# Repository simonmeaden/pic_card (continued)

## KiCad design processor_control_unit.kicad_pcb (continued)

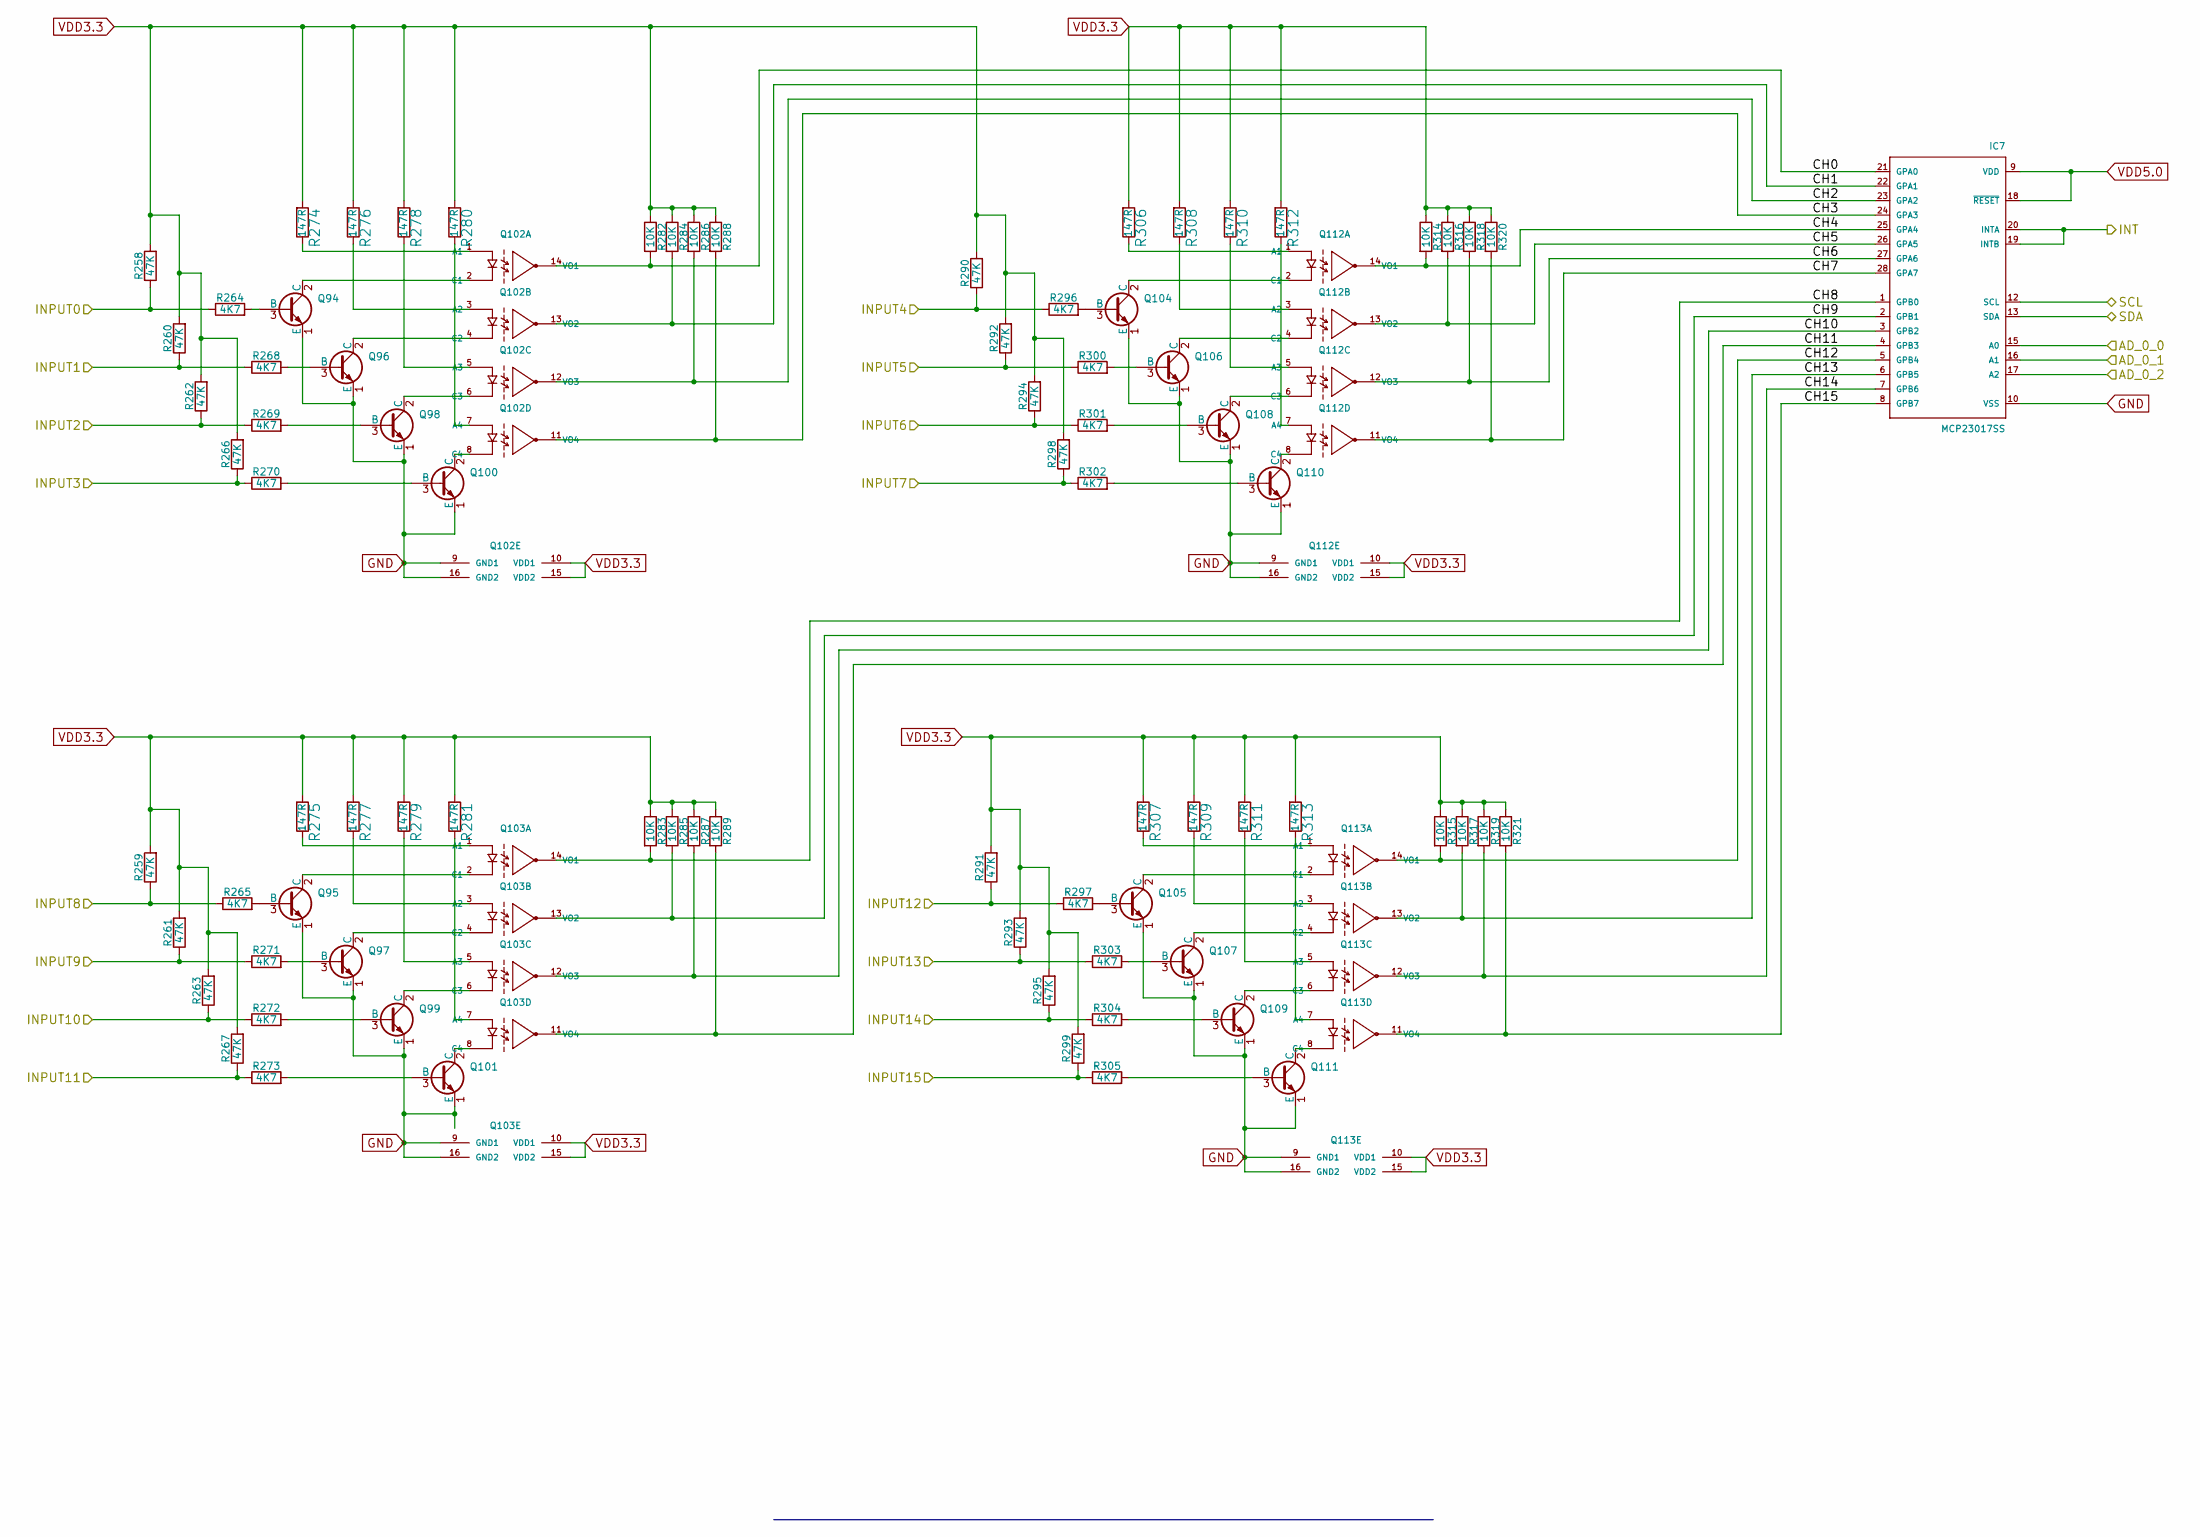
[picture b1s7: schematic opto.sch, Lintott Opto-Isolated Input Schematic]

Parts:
IC7: MCP23017SS; SSOP28
Q94, Q95, Q96, Q97, Q98, Q99, Q100, Q101, Q104, Q105, Q106, Q107, Q108, Q109, Q110, Q111: 2DD2656; SOT-323-DIODES_INC
Q102, Q103, Q112, Q113: ACSL-6400; SO-16-N
R258, R259, R260, R261, R262, R263, R266, R267, R290, R291, R292, R293, R294, R295, R298, R299: 47K; R_0805_2012Metric
R264, R265, R268, R269, R270, R271, R272, R273, R296, R297, R300, R301, R302, R303, R304, R305: 4K7; R_0805_2012Metric
R274, R275, R276, R277, R278, R279, R280, R281, R306, R307, R308, R309, R310, R311, R312, R313: 147R; R_0805_2012Metric
R282, R283, R284, R285, R286, R287, R288, R289, R314, R315, R316, R317, R318, R319, R320, R321: 10K; R_0805_2012Metric

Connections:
/IN-0: R258.1, R264.1; also elsewhere on the board
/IN-1: R260.1, R268.1; also elsewhere on the board
/IN-2: R262.1, R269.1; also elsewhere on the board
/IN-3: R266.1, R270.1; also elsewhere on the board
/IN-4: R290.1, R296.1; also elsewhere on the board
/IN-5: R292.1, R300.1; also elsewhere on the board
/IN-6: R294.1, R301.1; also elsewhere on the board
/IN-7: R298.1, R302.1; also elsewhere on the board
/IN-8: R259.1, R265.1; also elsewhere on the board
/IN-9: R261.1, R271.1; also elsewhere on the board
/IN-10: R263.1, R272.1; also elsewhere on the board
/IN-11: R267.1, R273.1; also elsewhere on the board
/IN-12: R291.1, R297.1; also elsewhere on the board
/IN-13: R293.1, R303.1; also elsewhere on the board
/IN-14: R295.1, R304.1; also elsewhere on the board
/IN-15: R299.1, R305.1; also elsewhere on the board
/Open Collector Buffered Outputs/SCL: IC7.12 (SCL); also elsewhere on the board
/Open Collector Buffered Outputs/SDA: IC7.13 (SDA); also elsewhere on the board
/Opto Isolated Inputs 1/CH0: IC7.21 (GPA0), Q102.14 (VO1), R282.2
/Opto Isolated Inputs 1/CH1: IC7.22 (GPA1), Q102.13 (VO2), R284.2
/Opto Isolated Inputs 1/CH2: IC7.23 (GPA2), Q102.12 (VO3), R286.2
/Opto Isolated Inputs 1/CH3: IC7.24 (GPA3), Q102.11 (VO4), R288.2
/Opto Isolated Inputs 1/CH4: IC7.25 (GPA4), Q112.14 (VO1), R314.2
/Opto Isolated Inputs 1/CH5: IC7.26 (GPA5), Q112.13 (VO2), R316.2
/Opto Isolated Inputs 1/CH6: IC7.27 (GPA6), Q112.12 (VO3), R318.2
/Opto Isolated Inputs 1/CH7: IC7.28 (GPA7), Q112.11 (VO4), R320.2
/Opto Isolated Inputs 1/CH8: IC7.1 (GPB0), Q103.14 (VO1), R283.2
/Opto Isolated Inputs 1/CH9: IC7.2 (GPB1), Q103.13 (VO2), R285.2
/Opto Isolated Inputs 1/CH10: IC7.3 (GPB2), Q103.12 (VO3), R287.2
/Opto Isolated Inputs 1/CH11: IC7.4 (GPB3), Q103.11 (VO4), R289.2
/Opto Isolated Inputs 1/CH12: IC7.5 (GPB4), Q113.14 (VO1), R315.2
/Opto Isolated Inputs 1/CH13: IC7.6 (GPB5), Q113.13 (VO2), R317.2
/Opto Isolated Inputs 1/CH14: IC7.7 (GPB6), Q113.12 (VO3), R319.2
/Opto Isolated Inputs 1/CH15: IC7.8 (GPB7), Q113.11 (VO4), R321.2
/Opto Isolated Inputs 1/INT: IC7.19 (INTB), IC7.20 (INTA); also elsewhere on the board
GND: IC7.10 (VSS), IC7.15 (A0), IC7.16 (A1), IC7.17 (A2), Q94.1 (E), Q95.1 (E), Q96.1 (E), Q97.1 (E), Q98.1 (E), Q99.1 (E), Q100.1 (E), Q101.1 (E), Q102.9 (GND1), Q102.16 (GND2), Q103.9 (GND1), Q103.16 (GND2), Q104.1 (E), Q105.1 (E), Q106.1 (E), Q107.1 (E), Q108.1 (E), Q109.1 (E), Q110.1 (E), Q111.1 (E), Q112.9 (GND1), Q112.16 (GND2), Q113.9 (GND1), Q113.16 (GND2); also elsewhere on the board
unnamed: Q94.3 (B), R264.2
unnamed: Q95.3 (B), R265.2
unnamed: Q96.3 (B), R268.2
unnamed: Q97.3 (B), R271.2
unnamed: Q98.3 (B), R269.2
unnamed: Q99.3 (B), R272.2
unnamed: Q100.2 (C), Q102.8 (C4)
unnamed: Q100.3 (B), R270.2
unnamed: Q101.2 (C), Q103.8 (C4)
unnamed: Q101.3 (B), R273.2
unnamed: Q102.1 (A1), R274.1
unnamed: Q94.2 (C), Q102.2 (C1)
unnamed: Q102.3 (A2), R276.1
unnamed: Q96.2 (C), Q102.4 (C2)
unnamed: Q102.5 (A3), R278.1
unnamed: Q98.2 (C), Q102.6 (C3)
unnamed: Q102.7 (A4), R280.1
unnamed: Q103.1 (A1), R275.1
unnamed: Q95.2 (C), Q103.2 (C1)
unnamed: Q103.3 (A2), R277.1
unnamed: Q97.2 (C), Q103.4 (C2)
unnamed: Q103.5 (A3), R279.1
unnamed: Q99.2 (C), Q103.6 (C3)
unnamed: Q103.7 (A4), R281.1
unnamed: Q104.2 (C), Q112.2 (C1)
unnamed: Q104.3 (B), R296.2
unnamed: Q105.2 (C), Q113.2 (C1)
unnamed: Q105.3 (B), R297.2
unnamed: Q106.2 (C), Q112.4 (C2)
unnamed: Q106.3 (B), R300.2
unnamed: Q107.2 (C), Q113.4 (C2)
unnamed: Q107.3 (B), R303.2
unnamed: Q108.2 (C), Q112.6 (C3)
unnamed: Q108.3 (B), R301.2
unnamed: Q109.2 (C), Q113.6 (C3)
unnamed: Q109.3 (B), R304.2
unnamed: Q110.2 (C), Q112.8 (C4)
unnamed: Q110.3 (B), R302.2
unnamed: Q111.2 (C), Q113.8 (C4)
unnamed: Q111.3 (B), R305.2
unnamed: Q112.1 (A1), R306.1
unnamed: Q112.3 (A2), R308.1
unnamed: Q112.5 (A3), R310.1
unnamed: Q112.7 (A4), R312.1
unnamed: Q113.1 (A1), R307.1
unnamed: Q113.3 (A2), R309.1
unnamed: Q113.5 (A3), R311.1
unnamed: Q113.7 (A4), R313.1
VDD3.3: Q102.10 (VDD1), Q102.15 (VDD2), Q103.10 (VDD1), Q103.15 (VDD2), Q112.10 (VDD1), Q112.15 (VDD2), Q113.10 (VDD1), Q113.15 (VDD2), R258.2, R259.2, R260.2, R261.2, R262.2, R263.2, R266.2, R267.2, R274.2, R275.2, R276.2, R277.2, R278.2, R279.2, R280.2, R281.2, R282.1, R283.1, R284.1, R285.1, R286.1, R287.1, R288.1, R289.1, R290.2, R291.2, R292.2, R293.2, R294.2, R295.2, R298.2, R299.2, R306.2, R307.2, R308.2, R309.2, R310.2, R311.2, R312.2, R313.2, R314.1, R315.1, R316.1, R317.1, R318.1, R319.1, R320.1, R321.1; also elsewhere on the board
VDD5.0: IC7.9 (VDD), IC7.18 (~RESET); also elsewhere on the board

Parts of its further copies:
IC4, IC5, IC6: MCP23017SS; SSOP28
Q34, Q35, Q36, Q37, Q38, Q39, Q40, Q41, Q44, Q45, Q46, Q47, Q48, Q49, Q50, Q51, Q54, Q55, Q56, Q57, Q58, Q59, Q60, Q61, Q64, Q65, Q66, Q67, Q68, Q69, Q70, Q71, Q74, Q75, Q76, Q77, Q78, Q79, Q80, Q81, Q84, Q85, Q86, Q87, Q88, Q89, Q90, Q91: 2DD2656; SOT-323-DIODES_INC
Q42, Q43, Q52, Q53, Q62, Q63, Q72, Q73, Q82, Q83, Q92, Q93: ACSL-6400; SO-16-N
R66, R67, R68, R69, R70, R71, R74, R75, R98, R99, R100, R101, R102, R103, R106, R107, R130, R131, R132, R133, R134, R135, R138, R139, R162, R163, R164, R165, R166, R167, R170, R171, R194, R195, R196, R197, R198, R199, R202, R203, R226, R227, R228, R229, R230, R231, R234, R235: 47K; R_0805_2012Metric
R72, R73, R76, R77, R78, R79, R80, R81, R104, R105, R108, R109, R110, R111, R112, R113, R136, R137, R140, R141, R142, R143, R144, R145, R168, R169, R172, R173, R174, R175, R176, R177, R200, R201, R204, R205, R206, R207, R208, R209, R232, R233, R236, R237, R238, R239, R240, R241: 4K7; R_0805_2012Metric
R82, R83, R84, R85, R86, R87, R88, R89, R114, R115, R116, R117, R118, R119, R120, R121, R146, R147, R148, R149, R150, R151, R152, R153, R178, R179, R180, R181, R182, R183, R184, R185, R210, R211, R212, R213, R214, R215, R216, R217, R242, R243, R244, R245, R246, R247, R248, R249: 147R; R_0805_2012Metric
R90, R91, R92, R93, R94, R95, R96, R97, R122, R123, R124, R125, R126, R127, R128, R129, R154, R155, R156, R157, R158, R159, R160, R161, R186, R187, R188, R189, R190, R191, R192, R193, R218, R219, R220, R221, R222, R223, R224, R225, R250, R251, R252, R253, R254, R255, R256, R257: 10K; R_0805_2012Metric

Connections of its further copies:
+5V: IC4.15 (A0), IC5.16 (A1), IC6.15 (A0), IC6.16 (A1); also elsewhere on the board
/IN-16: R66.1, R72.1; also elsewhere on the board
/IN-17: R68.1, R76.1; also elsewhere on the board
/IN-18: R70.1, R77.1; also elsewhere on the board
/IN-19: R74.1, R78.1; also elsewhere on the board
/IN-20: R98.1, R104.1; also elsewhere on the board
/IN-21: R100.1, R108.1; also elsewhere on the board
/IN-22: R102.1, R109.1; also elsewhere on the board
/IN-23: R106.1, R110.1; also elsewhere on the board
/IN-24: R67.1, R73.1; also elsewhere on the board
/IN-25: R69.1, R79.1; also elsewhere on the board
/IN-26: R71.1, R80.1; also elsewhere on the board
/IN-27: R75.1, R81.1; also elsewhere on the board
/IN-28: R99.1, R105.1; also elsewhere on the board
/IN-29: R101.1, R111.1; also elsewhere on the board
/IN-30: R103.1, R112.1; also elsewhere on the board
/IN-31: R107.1, R113.1; also elsewhere on the board
/IN-32: R130.1, R136.1; also elsewhere on the board
/IN-33: R132.1, R140.1; also elsewhere on the board
/IN-34: R134.1, R141.1; also elsewhere on the board
/IN-35: R138.1, R142.1; also elsewhere on the board
/IN-36: R162.1, R168.1; also elsewhere on the board
/IN-37: R164.1, R172.1; also elsewhere on the board
/IN-38: R166.1, R173.1; also elsewhere on the board
/IN-39: R170.1, R174.1; also elsewhere on the board
/IN-40: R131.1, R137.1; also elsewhere on the board
/IN-41: R133.1, R143.1; also elsewhere on the board
/IN-42: R135.1, R144.1; also elsewhere on the board
/IN-43: R139.1, R145.1; also elsewhere on the board
/IN-44: R163.1, R169.1; also elsewhere on the board
/IN-45: R165.1, R175.1; also elsewhere on the board
/IN-46: R167.1, R176.1; also elsewhere on the board
/IN-47: R171.1, R177.1; also elsewhere on the board
/IN-48: R194.1, R200.1; also elsewhere on the board
/IN-49: R196.1, R204.1; also elsewhere on the board
/IN-50: R198.1, R205.1; also elsewhere on the board
/IN-51: R202.1, R206.1; also elsewhere on the board
/IN-52: R226.1, R232.1; also elsewhere on the board
/IN-53: R228.1, R236.1; also elsewhere on the board
/IN-54: R230.1, R237.1; also elsewhere on the board
/IN-55: R234.1, R238.1; also elsewhere on the board
/IN-56: R195.1, R201.1; also elsewhere on the board
/IN-57: R197.1, R207.1; also elsewhere on the board
/IN-58: R199.1, R208.1; also elsewhere on the board
/IN-59: R203.1, R209.1; also elsewhere on the board
/IN-60: R227.1, R233.1; also elsewhere on the board
/IN-61: R229.1, R239.1; also elsewhere on the board
/IN-62: R231.1, R240.1; also elsewhere on the board
/IN-63: R235.1, R241.1; also elsewhere on the board
/Open Collector Buffered Outputs/SCL: IC4.12 (SCL), IC5.12 (SCL), IC6.12 (SCL); also elsewhere on the board
/Open Collector Buffered Outputs/SDA: IC4.13 (SDA), IC5.13 (SDA), IC6.13 (SDA); also elsewhere on the board
/Opto Isolated Inputs 2/CH0: IC4.21 (GPA0), Q42.14 (VO1), R90.2
/Opto Isolated Inputs 2/CH1: IC4.22 (GPA1), Q42.13 (VO2), R92.2
/Opto Isolated Inputs 2/CH2: IC4.23 (GPA2), Q42.12 (VO3), R94.2
/Opto Isolated Inputs 2/CH3: IC4.24 (GPA3), Q42.11 (VO4), R96.2
/Opto Isolated Inputs 2/CH4: IC4.25 (GPA4), Q52.14 (VO1), R122.2
/Opto Isolated Inputs 2/CH5: IC4.26 (GPA5), Q52.13 (VO2), R124.2
/Opto Isolated Inputs 2/CH6: IC4.27 (GPA6), Q52.12 (VO3), R126.2
/Opto Isolated Inputs 2/CH7: IC4.28 (GPA7), Q52.11 (VO4), R128.2
/Opto Isolated Inputs 2/CH8: IC4.1 (GPB0), Q43.14 (VO1), R91.2
/Opto Isolated Inputs 2/CH9: IC4.2 (GPB1), Q43.13 (VO2), R93.2
/Opto Isolated Inputs 2/CH10: IC4.3 (GPB2), Q43.12 (VO3), R95.2
/Opto Isolated Inputs 2/CH11: IC4.4 (GPB3), Q43.11 (VO4), R97.2
/Opto Isolated Inputs 2/CH12: IC4.5 (GPB4), Q53.14 (VO1), R123.2
/Opto Isolated Inputs 2/CH13: IC4.6 (GPB5), Q53.13 (VO2), R125.2
/Opto Isolated Inputs 2/CH14: IC4.7 (GPB6), Q53.12 (VO3), R127.2
/Opto Isolated Inputs 2/CH15: IC4.8 (GPB7), Q53.11 (VO4), R129.2
/Opto Isolated Inputs 2/INT: IC4.19 (INTB), IC4.20 (INTA); also elsewhere on the board
/Opto Isolated Inputs 3/CH0: IC5.21 (GPA0), Q62.14 (VO1), R154.2
/Opto Isolated Inputs 3/CH1: IC5.22 (GPA1), Q62.13 (VO2), R156.2
/Opto Isolated Inputs 3/CH2: IC5.23 (GPA2), Q62.12 (VO3), R158.2
/Opto Isolated Inputs 3/CH3: IC5.24 (GPA3), Q62.11 (VO4), R160.2
/Opto Isolated Inputs 3/CH4: IC5.25 (GPA4), Q72.14 (VO1), R186.2
/Opto Isolated Inputs 3/CH5: IC5.26 (GPA5), Q72.13 (VO2), R188.2
/Opto Isolated Inputs 3/CH6: IC5.27 (GPA6), Q72.12 (VO3), R190.2
/Opto Isolated Inputs 3/CH7: IC5.28 (GPA7), Q72.11 (VO4), R192.2
/Opto Isolated Inputs 3/CH8: IC5.1 (GPB0), Q63.14 (VO1), R155.2
/Opto Isolated Inputs 3/CH9: IC5.2 (GPB1), Q63.13 (VO2), R157.2
/Opto Isolated Inputs 3/CH10: IC5.3 (GPB2), Q63.12 (VO3), R159.2
/Opto Isolated Inputs 3/CH11: IC5.4 (GPB3), Q63.11 (VO4), R161.2
/Opto Isolated Inputs 3/CH12: IC5.5 (GPB4), Q73.14 (VO1), R187.2
/Opto Isolated Inputs 3/CH13: IC5.6 (GPB5), Q73.13 (VO2), R189.2
/Opto Isolated Inputs 3/CH14: IC5.7 (GPB6), Q73.12 (VO3), R191.2
/Opto Isolated Inputs 3/CH15: IC5.8 (GPB7), Q73.11 (VO4), R193.2
/Opto Isolated Inputs 3/INT: IC5.19 (INTB), IC5.20 (INTA); also elsewhere on the board
/Opto Isolated Inputs 4/CH0: IC6.21 (GPA0), Q82.14 (VO1), R218.2
/Opto Isolated Inputs 4/CH1: IC6.22 (GPA1), Q82.13 (VO2), R220.2
/Opto Isolated Inputs 4/CH2: IC6.23 (GPA2), Q82.12 (VO3), R222.2
/Opto Isolated Inputs 4/CH3: IC6.24 (GPA3), Q82.11 (VO4), R224.2
/Opto Isolated Inputs 4/CH4: IC6.25 (GPA4), Q92.14 (VO1), R250.2
/Opto Isolated Inputs 4/CH5: IC6.26 (GPA5), Q92.13 (VO2), R252.2
/Opto Isolated Inputs 4/CH6: IC6.27 (GPA6), Q92.12 (VO3), R254.2
/Opto Isolated Inputs 4/CH7: IC6.28 (GPA7), Q92.11 (VO4), R256.2
/Opto Isolated Inputs 4/CH8: IC6.1 (GPB0), Q83.14 (VO1), R219.2
/Opto Isolated Inputs 4/CH9: IC6.2 (GPB1), Q83.13 (VO2), R221.2
/Opto Isolated Inputs 4/CH10: IC6.3 (GPB2), Q83.12 (VO3), R223.2
/Opto Isolated Inputs 4/CH11: IC6.4 (GPB3), Q83.11 (VO4), R225.2
/Opto Isolated Inputs 4/CH12: IC6.5 (GPB4), Q93.14 (VO1), R251.2
/Opto Isolated Inputs 4/CH13: IC6.6 (GPB5), Q93.13 (VO2), R253.2
/Opto Isolated Inputs 4/CH14: IC6.7 (GPB6), Q93.12 (VO3), R255.2
/Opto Isolated Inputs 4/CH15: IC6.8 (GPB7), Q93.11 (VO4), R257.2
/Opto Isolated Inputs 4/INT: IC6.19 (INTB), IC6.20 (INTA); also elsewhere on the board
GND: IC4.10 (VSS), IC4.16 (A1), IC4.17 (A2), IC5.10 (VSS), IC5.15 (A0), IC5.17 (A2), IC6.10 (VSS), IC6.17 (A2), Q34.1 (E), Q35.1 (E), Q36.1 (E), Q37.1 (E), Q38.1 (E), Q39.1 (E), Q40.1 (E), Q41.1 (E), Q42.9 (GND1), Q42.16 (GND2), Q43.9 (GND1), Q43.16 (GND2), Q44.1 (E), Q45.1 (E), Q46.1 (E), Q47.1 (E), Q48.1 (E), Q49.1 (E), Q50.1 (E), Q51.1 (E), Q52.9 (GND1), Q52.16 (GND2), Q53.9 (GND1), Q53.16 (GND2), Q54.1 (E), Q55.1 (E), Q56.1 (E), Q57.1 (E), Q58.1 (E), Q59.1 (E), Q60.1 (E), Q61.1 (E), Q62.9 (GND1), Q62.16 (GND2), Q63.9 (GND1), Q63.16 (GND2), Q64.1 (E), Q65.1 (E), Q66.1 (E), Q67.1 (E), Q68.1 (E), Q69.1 (E), Q70.1 (E), Q71.1 (E), Q72.9 (GND1), Q72.16 (GND2), Q73.9 (GND1), Q73.16 (GND2), Q74.1 (E), Q75.1 (E), Q76.1 (E), Q77.1 (E), Q78.1 (E), Q79.1 (E), Q80.1 (E), Q81.1 (E), Q82.9 (GND1), Q82.16 (GND2), Q83.9 (GND1), Q83.16 (GND2), Q84.1 (E), Q85.1 (E), Q86.1 (E), Q87.1 (E), Q88.1 (E), Q89.1 (E), Q90.1 (E), Q91.1 (E), Q92.9 (GND1), Q92.16 (GND2), Q93.9 (GND1), Q93.16 (GND2); also elsewhere on the board
unnamed: Q34.2 (C), Q42.2 (C1)
unnamed: Q34.3 (B), R72.2
unnamed: Q35.2 (C), Q43.2 (C1)
unnamed: Q35.3 (B), R73.2
unnamed: Q36.2 (C), Q42.4 (C2)
unnamed: Q36.3 (B), R76.2
unnamed: Q37.2 (C), Q43.4 (C2)
unnamed: Q37.3 (B), R79.2
unnamed: Q38.2 (C), Q42.6 (C3)
unnamed: Q38.3 (B), R77.2
unnamed: Q39.2 (C), Q43.6 (C3)
unnamed: Q39.3 (B), R80.2
unnamed: Q40.2 (C), Q42.8 (C4)
unnamed: Q40.3 (B), R78.2
unnamed: Q41.2 (C), Q43.8 (C4)
unnamed: Q41.3 (B), R81.2
unnamed: Q42.1 (A1), R82.1
unnamed: Q42.3 (A2), R84.1
unnamed: Q42.5 (A3), R86.1
unnamed: Q42.7 (A4), R88.1
unnamed: Q43.1 (A1), R83.1
unnamed: Q43.3 (A2), R85.1
unnamed: Q43.5 (A3), R87.1
unnamed: Q43.7 (A4), R89.1
unnamed: Q44.2 (C), Q52.2 (C1)
unnamed: Q44.3 (B), R104.2
unnamed: Q45.2 (C), Q53.2 (C1)
unnamed: Q45.3 (B), R105.2
unnamed: Q46.2 (C), Q52.4 (C2)
unnamed: Q46.3 (B), R108.2
unnamed: Q47.2 (C), Q53.4 (C2)
unnamed: Q47.3 (B), R111.2
unnamed: Q48.2 (C), Q52.6 (C3)
unnamed: Q48.3 (B), R109.2
unnamed: Q49.2 (C), Q53.6 (C3)
unnamed: Q49.3 (B), R112.2
unnamed: Q50.2 (C), Q52.8 (C4)
unnamed: Q50.3 (B), R110.2
unnamed: Q51.2 (C), Q53.8 (C4)
unnamed: Q51.3 (B), R113.2
unnamed: Q52.1 (A1), R114.1
unnamed: Q52.3 (A2), R116.1
unnamed: Q52.5 (A3), R118.1
unnamed: Q52.7 (A4), R120.1
unnamed: Q53.1 (A1), R115.1
unnamed: Q53.3 (A2), R117.1
unnamed: Q53.5 (A3), R119.1
unnamed: Q53.7 (A4), R121.1
unnamed: Q54.2 (C), Q62.2 (C1)
unnamed: Q54.3 (B), R136.2
unnamed: Q55.2 (C), Q63.2 (C1)
unnamed: Q55.3 (B), R137.2
unnamed: Q56.2 (C), Q62.4 (C2)
unnamed: Q56.3 (B), R140.2
unnamed: Q57.2 (C), Q63.4 (C2)
unnamed: Q57.3 (B), R143.2
unnamed: Q58.2 (C), Q62.6 (C3)
unnamed: Q58.3 (B), R141.2
unnamed: Q59.2 (C), Q63.6 (C3)
unnamed: Q59.3 (B), R144.2
unnamed: Q60.2 (C), Q62.8 (C4)
unnamed: Q60.3 (B), R142.2
unnamed: Q61.2 (C), Q63.8 (C4)
unnamed: Q61.3 (B), R145.2
unnamed: Q62.1 (A1), R146.1
unnamed: Q62.3 (A2), R148.1
unnamed: Q62.5 (A3), R150.1
unnamed: Q62.7 (A4), R152.1
unnamed: Q63.1 (A1), R147.1
unnamed: Q63.3 (A2), R149.1
unnamed: Q63.5 (A3), R151.1
unnamed: Q63.7 (A4), R153.1
unnamed: Q64.2 (C), Q72.2 (C1)
unnamed: Q64.3 (B), R168.2
unnamed: Q65.2 (C), Q73.2 (C1)
unnamed: Q65.3 (B), R169.2
unnamed: Q66.2 (C), Q72.4 (C2)
unnamed: Q66.3 (B), R172.2
unnamed: Q67.2 (C), Q73.4 (C2)
unnamed: Q67.3 (B), R175.2
unnamed: Q68.2 (C), Q72.6 (C3)
unnamed: Q68.3 (B), R173.2
unnamed: Q69.2 (C), Q73.6 (C3)
unnamed: Q69.3 (B), R176.2
unnamed: Q70.2 (C), Q72.8 (C4)
unnamed: Q70.3 (B), R174.2
unnamed: Q71.2 (C), Q73.8 (C4)
unnamed: Q71.3 (B), R177.2
unnamed: Q72.1 (A1), R178.1
unnamed: Q72.3 (A2), R180.1
unnamed: Q72.5 (A3), R182.1
unnamed: Q72.7 (A4), R184.1
unnamed: Q73.1 (A1), R179.1
unnamed: Q73.3 (A2), R181.1
unnamed: Q73.5 (A3), R183.1
unnamed: Q73.7 (A4), R185.1
unnamed: Q74.2 (C), Q82.2 (C1)
unnamed: Q74.3 (B), R200.2
unnamed: Q75.2 (C), Q83.2 (C1)
unnamed: Q75.3 (B), R201.2
unnamed: Q76.2 (C), Q82.4 (C2)
unnamed: Q76.3 (B), R204.2
unnamed: Q77.2 (C), Q83.4 (C2)
unnamed: Q77.3 (B), R207.2
unnamed: Q78.2 (C), Q82.6 (C3)
unnamed: Q78.3 (B), R205.2
unnamed: Q79.2 (C), Q83.6 (C3)
unnamed: Q79.3 (B), R208.2
unnamed: Q80.2 (C), Q82.8 (C4)
unnamed: Q80.3 (B), R206.2
unnamed: Q81.2 (C), Q83.8 (C4)
unnamed: Q81.3 (B), R209.2
unnamed: Q82.1 (A1), R210.1
unnamed: Q82.3 (A2), R212.1
unnamed: Q82.5 (A3), R214.1
unnamed: Q82.7 (A4), R216.1
unnamed: Q83.1 (A1), R211.1
unnamed: Q83.3 (A2), R213.1
unnamed: Q83.5 (A3), R215.1
unnamed: Q83.7 (A4), R217.1
unnamed: Q84.2 (C), Q92.2 (C1)
unnamed: Q84.3 (B), R232.2
unnamed: Q85.2 (C), Q93.2 (C1)
unnamed: Q85.3 (B), R233.2
unnamed: Q86.2 (C), Q92.4 (C2)
unnamed: Q86.3 (B), R236.2
unnamed: Q87.2 (C), Q93.4 (C2)
unnamed: Q87.3 (B), R239.2
unnamed: Q88.2 (C), Q92.6 (C3)
unnamed: Q88.3 (B), R237.2
unnamed: Q89.2 (C), Q93.6 (C3)
unnamed: Q89.3 (B), R240.2
unnamed: Q90.2 (C), Q92.8 (C4)
unnamed: Q90.3 (B), R238.2
unnamed: Q91.2 (C), Q93.8 (C4)
unnamed: Q91.3 (B), R241.2
unnamed: Q92.1 (A1), R242.1
unnamed: Q92.3 (A2), R244.1
unnamed: Q92.5 (A3), R246.1
unnamed: Q92.7 (A4), R248.1
unnamed: Q93.1 (A1), R243.1
unnamed: Q93.3 (A2), R245.1
unnamed: Q93.5 (A3), R247.1
unnamed: Q93.7 (A4), R249.1
VDD3.3: Q42.10 (VDD1), Q42.15 (VDD2), Q43.10 (VDD1), Q43.15 (VDD2), Q52.10 (VDD1), Q52.15 (VDD2), Q53.10 (VDD1), Q53.15 (VDD2), Q62.10 (VDD1), Q62.15 (VDD2), Q63.10 (VDD1), Q63.15 (VDD2), Q72.10 (VDD1), Q72.15 (VDD2), Q73.10 (VDD1), Q73.15 (VDD2), Q82.10 (VDD1), Q82.15 (VDD2), Q83.10 (VDD1), Q83.15 (VDD2), Q92.10 (VDD1), Q92.15 (VDD2), Q93.10 (VDD1), Q93.15 (VDD2), R66.2, R67.2, R68.2, R69.2, R70.2, R71.2, R74.2, R75.2, R82.2, R83.2, R84.2, R85.2, R86.2, R87.2, R88.2, R89.2, R90.1, R91.1, R92.1, R93.1, R94.1, R95.1, R96.1, R97.1, R98.2, R99.2, R100.2, R101.2, R102.2, R103.2, R106.2, R107.2, R114.2, R115.2, R116.2, R117.2, R118.2, R119.2, R120.2, R121.2, R122.1, R123.1, R124.1, R125.1, R126.1, R127.1, R128.1, R129.1, R130.2, R131.2, R132.2, R133.2, R134.2, R135.2, R138.2, R139.2, R146.2, R147.2, R148.2, R149.2, R150.2, R151.2, R152.2, R153.2, R154.1, R155.1, R156.1, R157.1, R158.1, R159.1, R160.1, R161.1, R162.2, R163.2, R164.2, R165.2, R166.2, R167.2, R170.2, R171.2, R178.2, R179.2, R180.2, R181.2, R182.2, R183.2, R184.2, R185.2, R186.1, R187.1, R188.1, R189.1, R190.1, R191.1, R192.1, R193.1, R194.2, R195.2, R196.2, R197.2, R198.2, R199.2, R202.2, R203.2, R210.2, R211.2, R212.2, R213.2, R214.2, R215.2, R216.2, R217.2, R218.1, R219.1, R220.1, R221.1, R222.1, R223.1, R224.1, R225.1, R226.2, R227.2, R228.2, R229.2, R230.2, R231.2, R234.2, R235.2, R242.2, R243.2, R244.2, R245.2, R246.2, R247.2, R248.2, R249.2, R250.1, R251.1, R252.1, R253.1, R254.1, R255.1, R256.1, R257.1; also elsewhere on the board
VDD5.0: IC4.9 (VDD), IC4.18 (~RESET), IC5.9 (VDD), IC5.18 (~RESET), IC6.9 (VDD), IC6.18 (~RESET); also elsewhere on the board

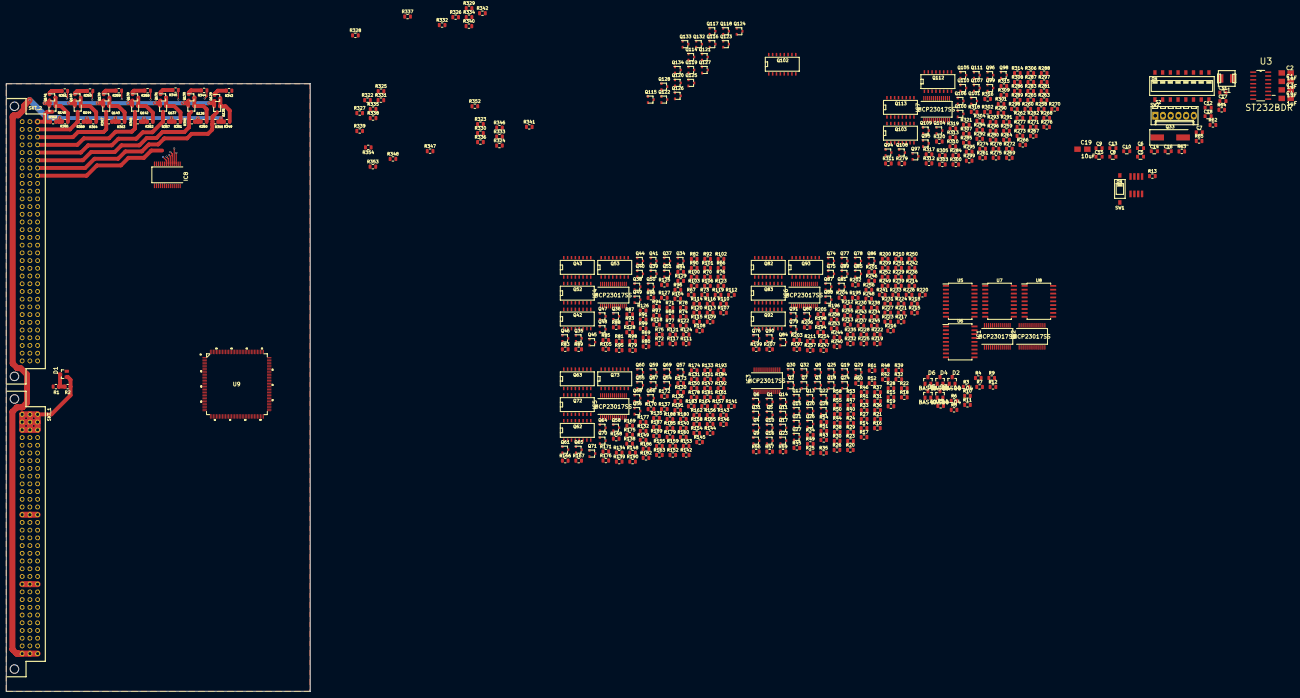
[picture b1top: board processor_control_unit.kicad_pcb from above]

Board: 4 copper layers, 100.0 x 200.0 mm, 560 parts (0 on the bottom side), 578 nets.

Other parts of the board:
C5: 0.01uF; C_0805
C6, C7, C8, C9, C10, C11, C13, C14, C15: 0.1uF; C_0805
C12, C16: 18pF; C_0805
C17: 10nF; C_0805
C18: 100nF; C_0805
C19: 10uF; Kemet_B_3528-21W
L1: 2.2Uh; Inductor_Vishay_IHLP-2020BZ-11_Series
Q33: 24MHz; Crystal_SMD_HC49-SD
R62: 10K0; R_0805_2012Metric
R63: 1K0; R_0805_2012Metric
R64, R65: 2K7; R_0805_2012Metric
S2: ICSP; Molex_KK-6410-06_06x2.54mm_Straight
SW2: ID_Switch; OMRON_A6S-810X-H_8xSPST
U9: PIC32MZXXXXEC_G_H_M_144-I_PLLQFP144_20X20MC-M; LQFP144_20X20MC

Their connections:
/Analogue Inputs/AD0: U9.36; also elsewhere on the board
/Analogue Inputs/AD1: U9.35; also elsewhere on the board
/Analogue Inputs/AD2: U9.34; also elsewhere on the board
/Analogue Inputs/AD3: U9.31; also elsewhere on the board
/Analogue Inputs/AD4: U9.26; also elsewhere on the board
/Analogue Inputs/AD5: U9.49; also elsewhere on the board
/CAN_N: U9.99; also elsewhere on the board
/CAN_P: U9.98; also elsewhere on the board
/Opto Isolated Inputs 1/INT: U9.79; also elsewhere on the board
/Opto Isolated Inputs 2/INT: U9.80; also elsewhere on the board
/Opto Isolated Inputs 3/INT: U9.106; also elsewhere on the board
/Opto Isolated Inputs 4/INT: U9.105; also elsewhere on the board
/Processor Control Unit/232-RX: U9.16; also elsewhere on the board
/Processor Control Unit/232-TX: U9.15; also elsewhere on the board
/Processor Control Unit/232-~CTS~: U9.23; also elsewhere on the board
/Processor Control Unit/232-~RTS~: U9.14; also elsewhere on the board
/Processor Control Unit/485-FAULT: U9.7; also elsewhere on the board
/Processor Control Unit/485-RX: U9.62; also elsewhere on the board
/Processor Control Unit/485-RX_TX_Enable: U9.8; also elsewhere on the board
/Processor Control Unit/485-TX: U9.61; also elsewhere on the board
/Processor Control Unit/MCLR: R63.2, S2.1, U9.20
/Processor Control Unit/OSC0: C12.2, Q33.1, U9.72
/Processor Control Unit/OSC1: C16.2, Q33.2, U9.71
/Processor Control Unit/PGEC: S2.5, U9.37
/Processor Control Unit/PGED: S2.4, U9.38
/Processor Control Unit/SCL: R65.1, U9.95
/Processor Control Unit/SDA: R64.1, U9.96
/USB_D+: U9.77; also elsewhere on the board
/USB_D-: U9.76; also elsewhere on the board
GND: C5.2, C6.1, C7.1, C8.2, C9.2, C10.2, C11.2, C12.1, C13.2, C14.2, C15.2, C16.1, C17.1, C18.1, C19.2, S2.3, U9.17, U9.32, U9.42, U9.54, U9.63, U9.75, U9.89, U9.108, U9.123, U9.136; also elsewhere on the board
unnamed: C5.1, R62.1, R63.1
unnamed: C17.2, C18.2, C19.1, L1.2, U9.41
unnamed: SW2.9, U9.68
unnamed: SW2.10, U9.67
unnamed: SW2.11, U9.66
unnamed: SW2.12, U9.65
unnamed: SW2.13, U9.46
unnamed: SW2.14, U9.45
unnamed: SW2.15, U9.44
unnamed: SW2.16, U9.43
VDD3.3: C6.2, C7.2, C8.1, C9.1, C10.1, C11.1, C13.1, C14.1, C15.1, L1.1, R62.2, S2.2, SW2.1, SW2.2, SW2.3, SW2.4, SW2.5, SW2.6, SW2.7, SW2.8, U9.18, U9.33, U9.55, U9.64, U9.74, U9.88, U9.107, U9.122, U9.137; also elsewhere on the board
VDD5.0: R64.2, R65.2, U9.73; also elsewhere on the board

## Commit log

2019-11-23 Initial commit of schematics/pcb.
2019-11-23 removed stored datasheets.
2019-11-23 Readme added.
